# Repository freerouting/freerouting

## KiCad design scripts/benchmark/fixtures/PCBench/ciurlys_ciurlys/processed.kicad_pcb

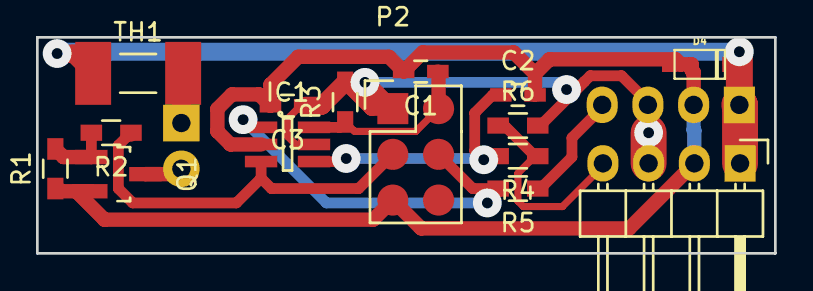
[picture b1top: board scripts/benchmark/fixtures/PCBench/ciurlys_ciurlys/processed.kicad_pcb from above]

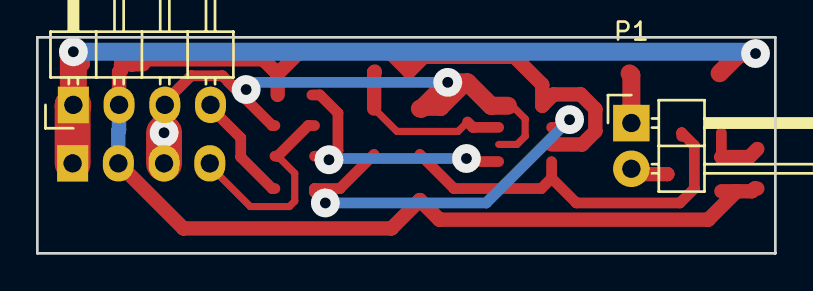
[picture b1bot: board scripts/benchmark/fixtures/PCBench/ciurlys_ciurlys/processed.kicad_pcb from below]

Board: 2 copper layers, 41.0 x 12.0 mm, 17 parts (2 on the bottom side), 12 nets.

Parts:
C1, C2, C3: C; C_0603_HandSoldering
D4: TRANSIL; sod123
IC1: ATTINY9-TS; SOT-23-6
P1: CONN_01X02; Pin_Header_Angled_1x02
P2: TPI; Pin_Header_Straight_2x03
P3: OUTPUT; Pin_Header_Angled_1x04
P4: INPUT; Pin_Header_Angled_1x04
Q1: Q_NMOS_GSD; SOT-23_Handsoldering
R1, R3, R6: 10k; R_0603_HandSoldering
R2: 330; R_0603_HandSoldering
R4, R5: 1k; R_0603_HandSoldering
TH1: THERMISTOR; R_1206_HandSoldering

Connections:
GND: C1.2, C2.2, C3.2, D4.1, IC1.2, P2.5, P3.2, P4.2, Q1.2, R1.1
unnamed: C1.1, IC1.6, P2.2, R3.1
unnamed: C2.1, IC1.4, R4.2
unnamed: P4.4, R4.1, R6.1
unnamed: P3.4, R5.1
unnamed: IC1.1, P2.4, R5.2
unnamed: IC1.3, P2.3, R2.1
unnamed: P1.1, TH1.2
unnamed: P1.2, Q1.3
unnamed: Q1.1, R1.2, R2.2
VCC: C3.1, IC1.5, P2.1, P3.3, P4.3, R3.2, R6.2
VDD: D4.2, P3.1, P4.1, TH1.1

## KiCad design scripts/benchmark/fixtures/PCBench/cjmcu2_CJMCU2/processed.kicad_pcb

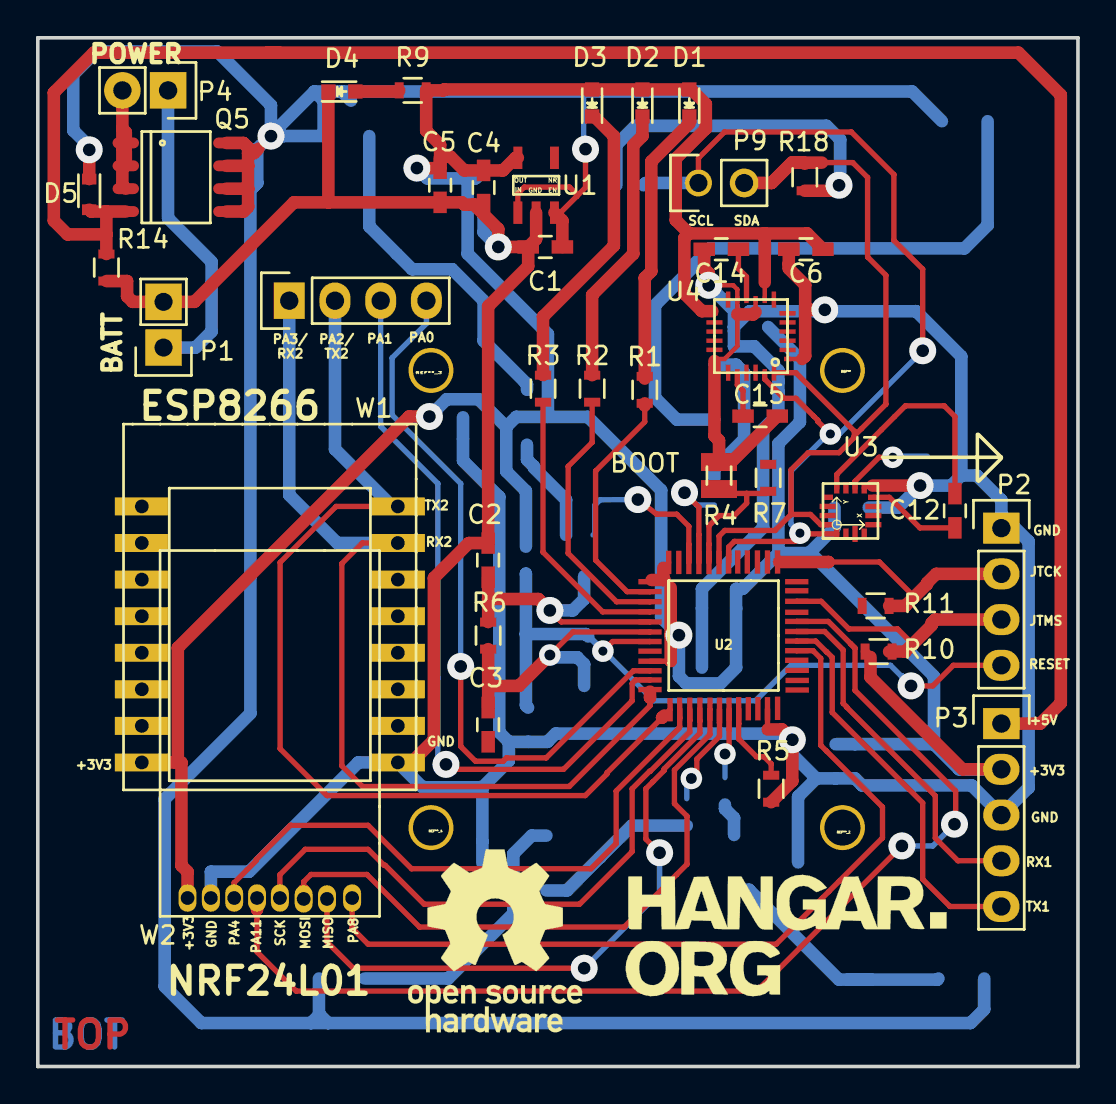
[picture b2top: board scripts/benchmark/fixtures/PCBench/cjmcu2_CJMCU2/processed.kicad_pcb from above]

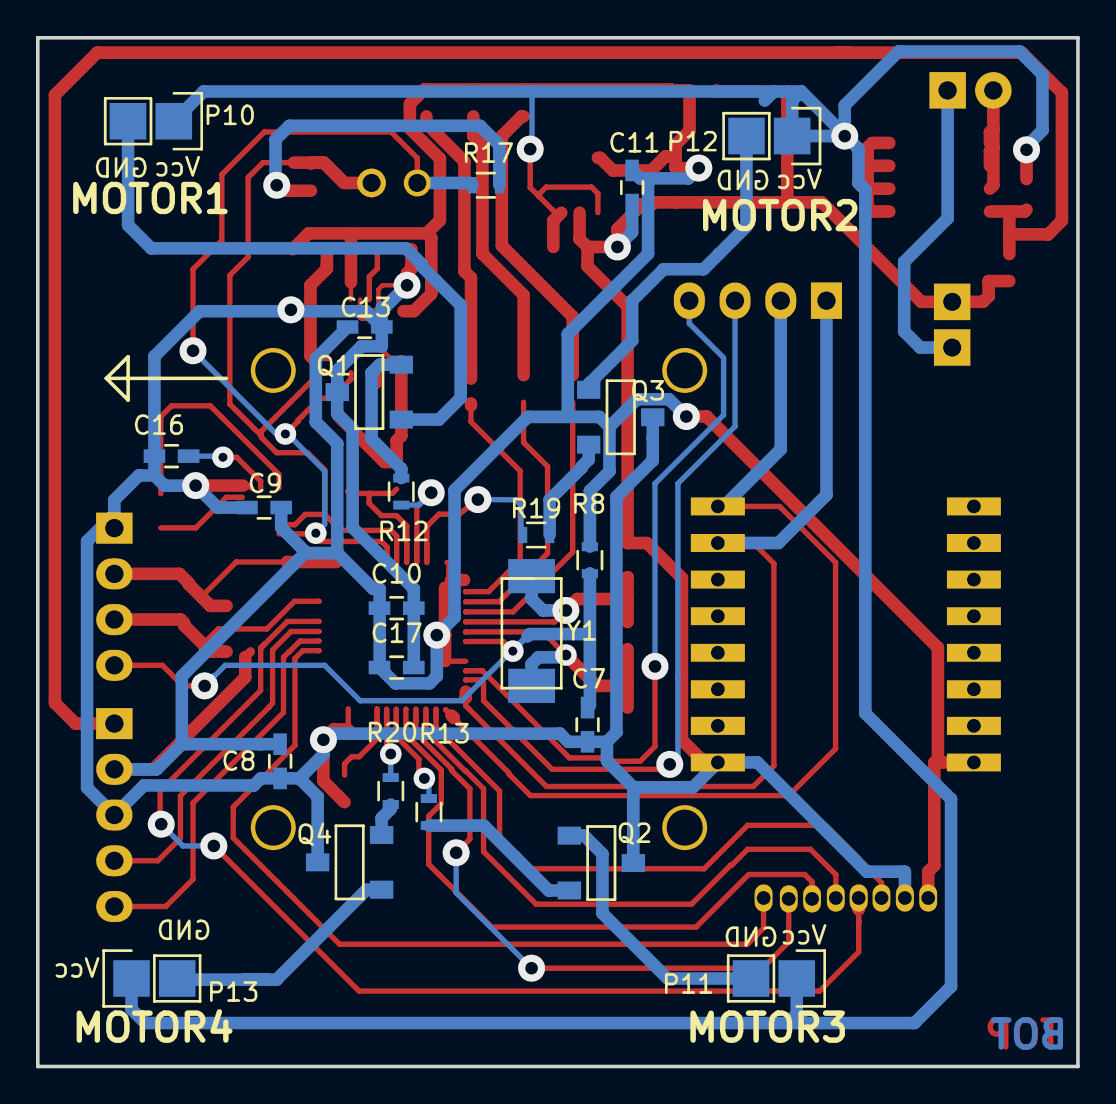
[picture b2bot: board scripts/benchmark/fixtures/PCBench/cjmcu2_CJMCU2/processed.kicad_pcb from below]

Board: 2 copper layers, 57.8 x 57.2 mm, 62 parts (23 on the bottom side), 52 nets.

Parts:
C1, C16: 4,7uF; C_0603_HandSoldering
C2, C3: 22pF; C_0603_HandSoldering
C4: 475; C_0603_HandSoldering
C5, C6, C7, C8, C9, C10, C11, C14, C17: 0,1uF; C_0603_HandSoldering
C12: 0,22uF; C_0603_HandSoldering
C13: 10nF; C_0603_HandSoldering
C15: 2,2nF; C_0603_HandSoldering
D1, D2, D3, D4: LED; LED_0603
D5: D; D_0603
P1, P4, P9, P10, P11, P12, P13: CONN_01X02; Pin_Header_Straight_1x02
P2: CONN_01X04; Pin_Header_Straight_1x04
P3: CONN_01X05; Pin_Header_Straight_1x05
P14: Pin_Header_Straight_1x04
Q1, Q2, Q3, Q4: IRLML2502; SOT_23
Q5: Q_PMOS_DGS; SO-8
R1, R2, R3: 551; R_0603
R4: 0; R_0603
R5, R7, R8, R10, R11, R14, R17, R18: 10k; R_0603
R6: 1M; R_0603
R9: 1k; R_0603
R12, R13, R19, R20: 20k; R_0603
U1: TPS73033DBVT
U2: STM32F103C8T6
U3: HMC5883L
U4: MPU6050; ttnlt745pv
W1: ESP8266(TX&RX); WIFI
W2: NRF24L01; nrf
Y1: 8MHz; crystal-ABM

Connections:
+3V3: C4.1, C5.1, C6.1, C8.1, C9.1, C10.1, C11.1, C13.1, C17.1, D1.2, D2.2, D3.2, P3.2, R8.2, R9.2, R10.1, U1.5, U2.1, U2.9, U2.48, U4.8, U4.13, W1.10, W2.4
+5V: D5.2, P3.1, Q5.4, R14.2
+BATT: P1.1, P4.1
/BOOT1: R5.2, U2.20
/PA4: U2.14, W2.6
/PA5/SP11_SCK: U2.15, W2.7
/PA6/SP11_MISO: U2.16, W2.8
/PA7/SP11_MOSI: U2.17, W2.2
/PA8: U2.29, W2.1
/PA9/USART1__TX: P3.5, U2.30
/PA10/USART1_RX: P3.4, U2.31
/PA11: U2.32, W2.3
/PA13_JTMS: P2.3, R10.2, U2.34
/PA14_JTCK: P2.2, R11.2, U2.37
/PB0: R13.2, U2.18
/PB1: R20.1, U2.19
/PB8: R12.2, U2.45
/PB9: R19.1, U2.46
/PC13: R1.1, U2.2
/PC14: R2.1, U2.3
/PC15: R3.2, U2.4
/RESET: C7.1, P2.4, R8.1, U2.7
/SCL: P9.1, R17.2, U2.42, U3.1, U4.23
/SDA: P9.2, R18.2, U2.43, U3.16, U4.24
/SETC: C12.2, U3.12
GND: C1.2, C2.1, C4.2, C5.2, C6.2, C7.2, C8.2, C9.2, C10.2, C11.2, C13.2, C14.2, C15.1, C16.1, C17.2, D4.1, P1.2, P2.1, P3.3, Q1.3, Q2.3, Q3.3, Q4.3, R4.1, R5.1, R14.1, U1.3, U2.23, U3.9, U4.1, U4.9, U4.11, U4.18, W1.2, W2.5
unnamed: C2.2, R6.1, U2.5, Y1.1
unnamed: C3.1, R6.2, U2.6, Y1.2
unnamed: C12.1, U3.8
unnamed: C14.1, U4.10
unnamed: C15.2, U4.20
unnamed: C16.2, U3.10
unnamed: D1.1, R1.2
unnamed: D2.1, R2.2
unnamed: D3.1, R3.1
unnamed: D4.2, R9.1
unnamed: P4.2, Q5.1, Q5.2, Q5.3
unnamed: P10.2, Q1.1
unnamed: P11.2, Q2.1
unnamed: P12.2, Q3.1
unnamed: P13.2, Q4.1
unnamed: Q1.2, R12.1
unnamed: Q2.2, R13.1
unnamed: Q3.2, R19.2
unnamed: Q4.2, R20.2
unnamed: R7.1, U2.44
unnamed: R17.1, R18.1
unnamed: P14.1, U2.12, W1.8
unnamed: P14.2, U2.13, W1.9
unnamed: P14.4, U2.10
unnamed: P14.3, U2.11
VCC: C1.1, D5.1, P10.1, P11.1, P12.1, P13.1, Q5.5, Q5.6, Q5.7, Q5.8, U1.1, U1.2

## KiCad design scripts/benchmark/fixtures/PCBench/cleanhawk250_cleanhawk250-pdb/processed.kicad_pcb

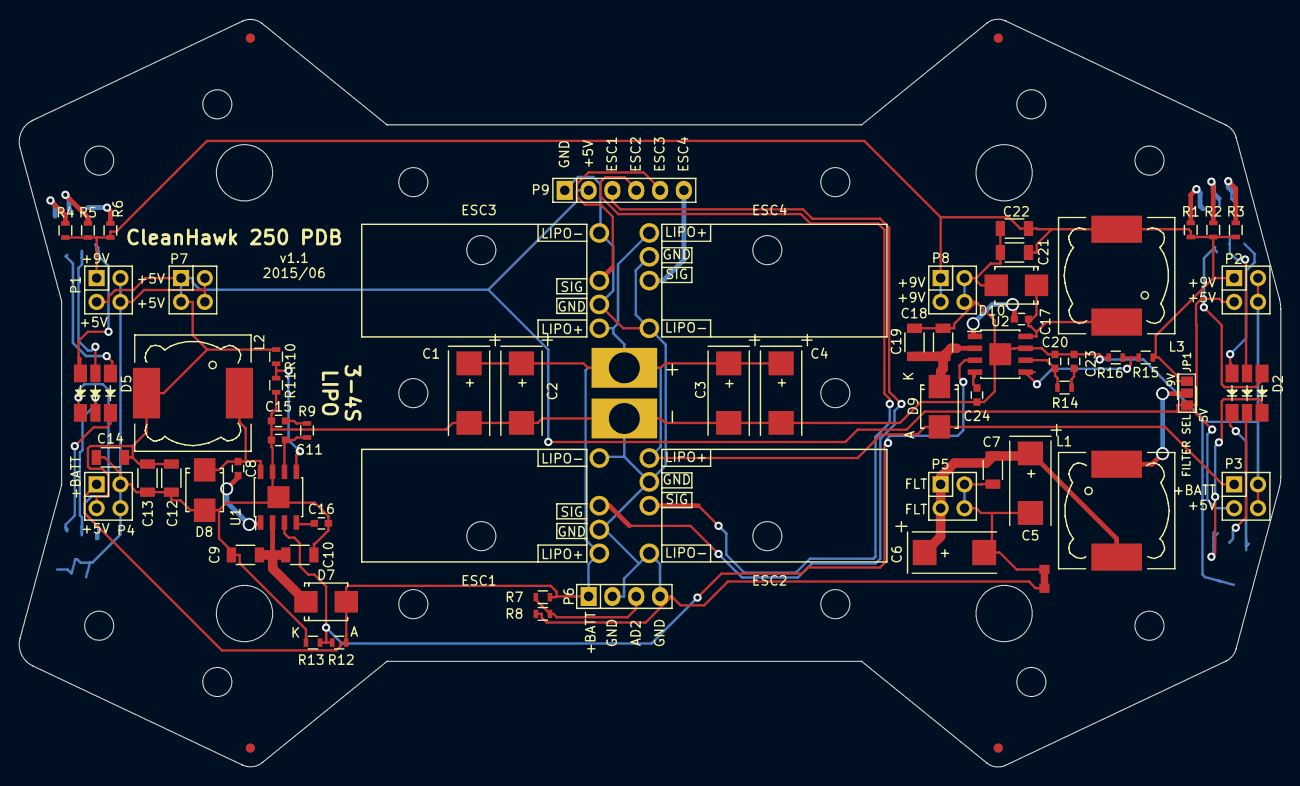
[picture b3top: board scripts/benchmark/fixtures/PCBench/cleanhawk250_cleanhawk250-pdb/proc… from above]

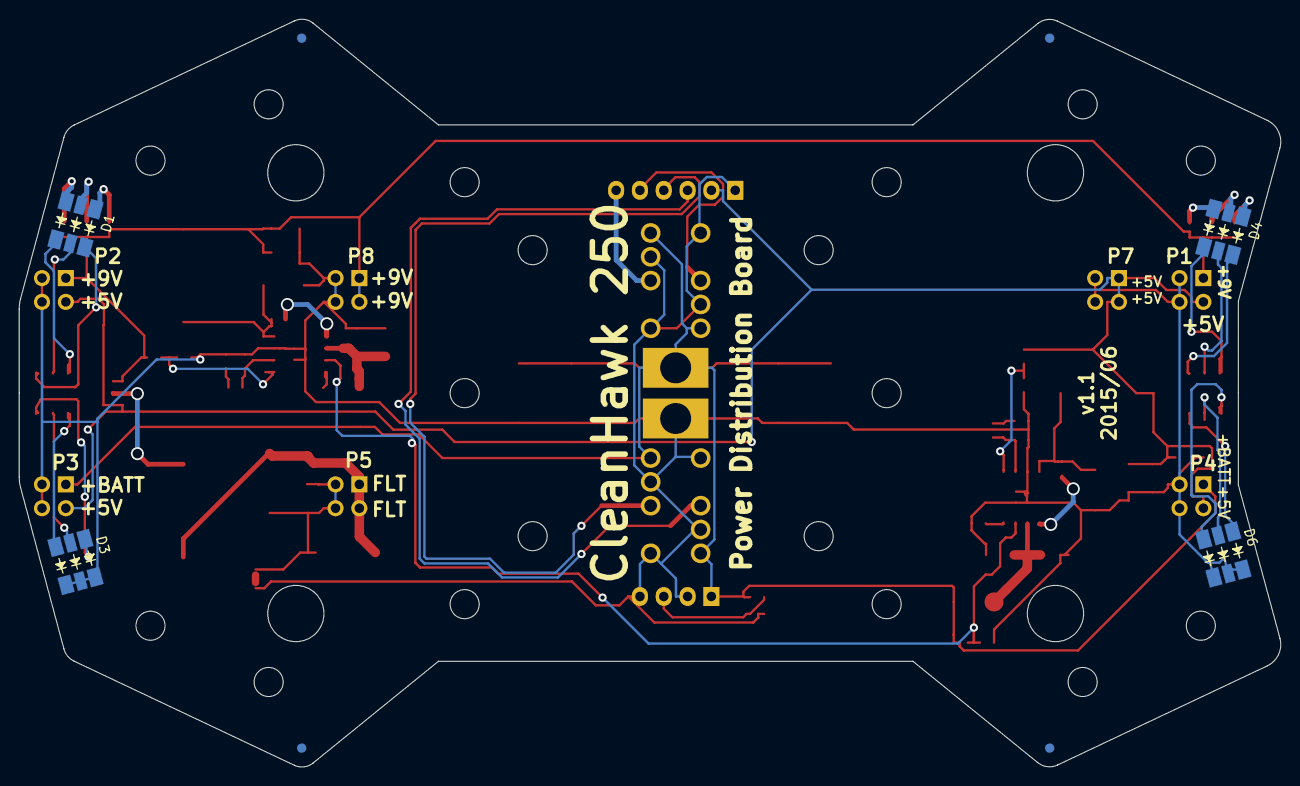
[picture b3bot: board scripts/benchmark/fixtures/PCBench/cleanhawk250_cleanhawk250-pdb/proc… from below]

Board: 2 copper layers, 134.5 x 79.7 mm, 80 parts (8 on the bottom side), 45 nets.

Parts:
C1, C2, C3, C4: 33uF/25V/np; TantalC_SizeD_EIA-7343_Reflow
C5, C6: 100uF/16V; TantalC_SizeD_EIA-7343_Reflow
C7, C9, C10, C18, C19: 10uF/35V; C_1206
C8, C17: 100nF; C_0603
C11, C20: 18pF; C_0603
C12, C13, C14: 22uF/10V; C_1206
C15, C23: 680pF; C_0603
C16, C24: 8.2nF; C_0603
C21, C22: 22uF/16V; C_1206
D1, D2, D3, D4, D5, D6: RGB_LED_5050; LED_5050_RGB
D7, D8, D9, D10: B340LB; Diode-SMB_Standard
ESC1, ESC2, ESC3, ESC4: KISS_ESC_18A; Kiss_ESC_18A_v1.1
F1, F2, F3, F4, F5, F6, F7, F8: SPECIAL; FIDUCIAL_1MM
FRAME1: SPECIAL; Emax250_Bottom_Holes
JP1: FILTER SEL; AB2_SJMP_03-1
JP2: JUMPER; NetTie-I_Connected_SMD
L1: 820uH; Choke_SMD_12x12mm_h6mm
L2, L3: 8.2uH; Choke_SMD_12x12mm_h6mm
P1, P2, P3, P4, P5, P7, P8: CONN_02X02; Pin_Header_Straight_2x02
P6: CONN_01X04; Pin_Header_Straight_1x04
P9: CONN_01X06; Pin_Header_Straight_1x06
R1, R3: 68; R_0603
R2, R5: 120; R_0603
R4, R6: 68/np; R_0603
R7, R10, R15: 10k/1%; R_0603
R8: 2.32k/1%; R_0603
R9, R14: 78.7k; R_0603
R11: 1.91k/1%; R_0603
R12: 169k/np; R_0603
R13: 28k/np; R_0603
R16: 976/1%; R_0603
U1, U2: TPS54331; SOIC-8-1EP_3.9x4.9mm_Pitch1.27mm
W1: WIREPADS; WirePads_12AWG_TH

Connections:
+5V: C12.1, C13.1, C14.1, JP1.3, L2.2, P1.3, P2.3, P3.3, P4.3, P7.1, P7.3, P9.2, R10.1
+9V: C21.1, C22.1, JP1.1, L3.2, P1.1, P2.1, P8.1, P8.3, R1.2, R2.2, R3.2, R4.2, R5.2, R6.2, R15.1
+BATT: C1.1, C2.1, C3.1, C4.1, D7.2, D9.2, ESC1.1, ESC2.1, ESC3.1, ESC4.1, P3.1, P4.1, P6.1, R7.2, R12.1, W1.+
ESC1: ESC1.2, P9.3
ESC2: ESC2.2, P9.4
ESC3: ESC3.2, P9.5
ESC4: ESC4.2, P9.6
GND: C1.2, C2.2, C3.2, C4.2, C9.2, C10.2, C11.2, C12.2, C13.2, C14.2, C15.2, C16.2, C18.2, C19.2, C20.2, C21.2, C22.2, C23.2, C24.2, D3.4, D3.5, D3.6, D6.4, D6.5, D6.6, D8.2, D10.2, ESC1.3, ESC1.4, ESC2.3, ESC2.4, ESC3.3, ESC3.4, ESC4.3, ESC4.4, JP2.1, P1.2, P1.4, P2.2, P2.4, P3.2, P3.4, P4.2, P4.4, P6.2, P6.4, P7.2, P7.4, P8.2, P8.4, P9.1, R8.2, R11.2, R13.2, R16.2, U1.7, U1.9, U2.7, U2.9, W1.-
GNDA: C5.2, C6.2, C7.2, JP2.2, P5.2, P5.4
unnamed: C5.1, C6.1, C7.1, L1.2, P5.1, P5.3
unnamed: C8.1, U1.1
unnamed: C8.2, D8.1, L2.1, U1.8
unnamed: C9.1, C10.1, D7.1, U1.2
unnamed: C11.1, R9.1, U1.6
unnamed: C15.1, R9.2
unnamed: C16.1, U1.4
unnamed: C17.1, U2.1
unnamed: C17.2, D10.1, L3.1, U2.8
unnamed: C18.1, C19.1, D9.1, U2.2
unnamed: C20.1, R14.1, U2.6
unnamed: C23.1, R14.2
unnamed: C24.1, U2.4
unnamed: D1.1, R1.1
unnamed: D1.2, R2.1
unnamed: D1.3, R3.1
unnamed: D1.4, D2.3
unnamed: D1.5, D2.2
unnamed: D1.6, D2.1
unnamed: D2.4, D3.3
unnamed: D2.5, D3.2
unnamed: D2.6, D3.1
unnamed: D4.1, R4.1
unnamed: D4.2, R5.1
unnamed: D4.3, R6.1
unnamed: D4.4, D5.3
unnamed: D4.5, D5.2
unnamed: D4.6, D5.1
unnamed: D5.4, D6.3
unnamed: D5.5, D6.2
unnamed: D5.6, D6.1
unnamed: JP1.2, L1.1
unnamed: P6.3, R7.1, R8.1
unnamed: R10.2, R11.1, U1.5
unnamed: R15.2, R16.1, U2.5
REG_EN: R12.2, R13.1, U1.3, U2.3
